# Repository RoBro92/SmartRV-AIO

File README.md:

# SmartRV AIO
**A ESP32 based smart home control board for a Camper/RV**

All feature requests are tracked in the GitHub issue tracker. 
[Feature Requests](https://github.com/RoBro92/feature-requests/issues)

This AIO board is planned to be able to work standalone or as part of a connected smart home network within a camper or RV. It will be designed based on suggestions from the community. As technology advances many are looking to automate tasks in day to day life, your recreational vehicle should be no different. Many existing monitoring systems are generally either very dated, or not very smart. This board will facilitate an all in one monitoring and control hub. 

The module has been kept as compact as possible and allows for a direct connection to 12v or 24v vehicle systems. 

**If you want to support the development you can purchase this board as a DIY kit or assembled from my Ko-Fi Shop [SmartRV Shop](https://ko-fi.com/smartrv/shop)**

## **I have developed two seperate versions of this module**

[AIO1 is THT and is suitable for at home soldering](#aio1)

[AIO2 is SMD and is designed to be assembled by a PCB manufacturer](#aio2)

###AIO1

# **THT Version 0.1**
This is the pre production initial design files with planned features and initial designs.

# **Features**
- [x] - ESP32 Microcontroller
- [x] - Individually controlled relays
- [x] - Input buttons 
- [x] - Tank temperature inputs
- [x] - Tank level inputs
- [x] - Auxilliary temperature & humidity input
- [x] - Spotlights/LED control & dimming
- [x] - RJ45 Output to Nextion Display
- [x] - Relay 1&2 are 12v direct supply for low current device 

# **Upcoming Changes**

- [ ] - RS485 serial connection
- [ ] - Bluetooth App
- [ ] - Bluetooth connection to external modules(such as Water tank module)
- [ ] - House battery voltage
- [ ] - Main battery voltage
- [ ] - On board programming
- [ ] - MQTT integration
- [ ] - Diesel heater control 

# **Images**

<table>
  <tr>
    <td>Schematic</td>
     <td>PCB Layout</td>
  </tr>
  <tr>
    <td></td>
    <td></td>
  </tr>
 </table>

# **WARNING**
This board does not have any fuse protection as such this must be provided externally.

###AIO2

# **SMD Version 0.1**
This is the pre production SMD initial design files with planned features and initial designs.

# **Features**
- [x] - ESP32 Microcontroller
- [x] - Individually controlled relays
- [x] - Input buttons 
- [x] - Tank temperature inputs
- [x] - Tank level inputs
- [x] - Auxilliary temperature & humidity input

# **Upcoming Changes**

- [ ] - RS485 serial connection
- [ ] - Bluetooth App
- [ ] - Bluetooth connection to external modules(such as Water tank module)
- [ ] - House battery voltage
- [ ] - Main battery voltage
- [ ] - On board programming
- [ ] - MQTT integration
- [ ] - Diesel heater control 
- [ ] - RJ45 Output to Nextion Display
- [ ] - Spotlights/LED control & dimming
- [ ] - Relay 1&2 are 12v direct supply for low current device 

# **Images**

<table>
  <tr>
    <td>Schematic</td>
     <td>PCB Layout</td>
  </tr>
  <tr>
    <td></td>
    <td></td>
  </tr>
 </table>

# **WARNING**
This board does not have any fuse protection as such this must be provided externally.

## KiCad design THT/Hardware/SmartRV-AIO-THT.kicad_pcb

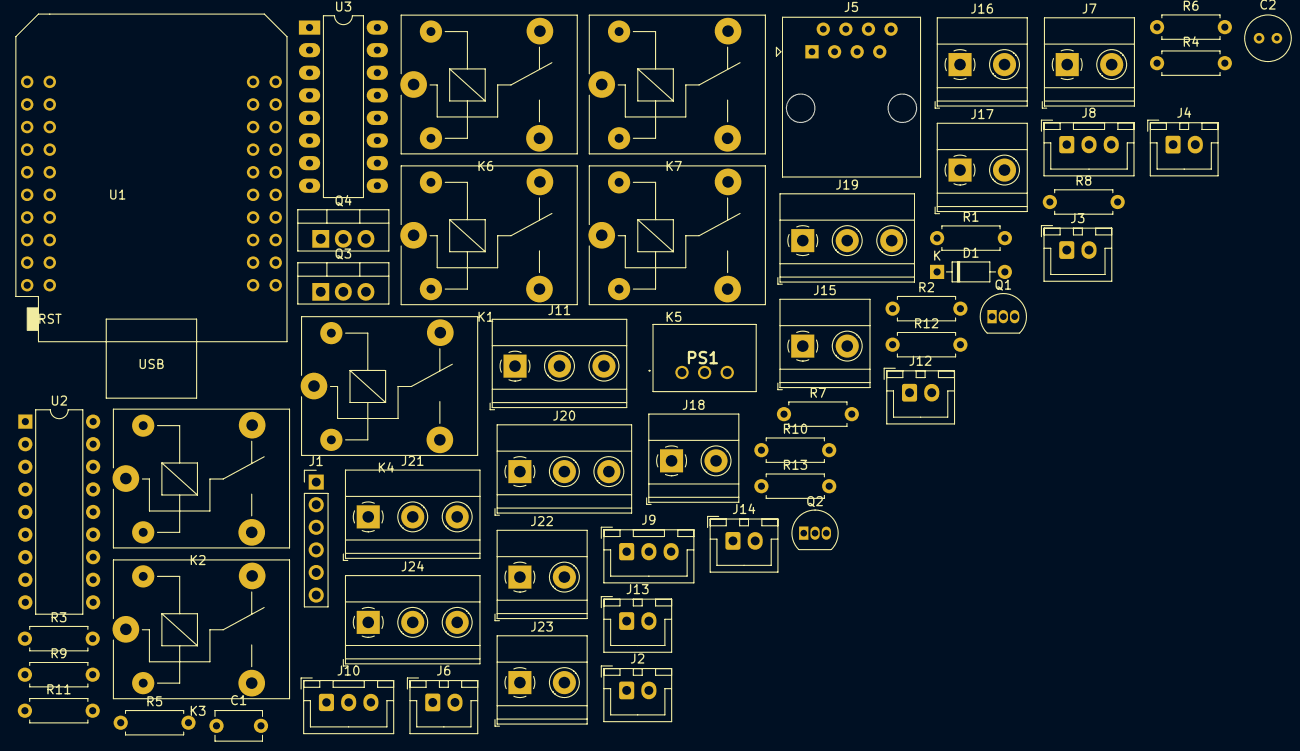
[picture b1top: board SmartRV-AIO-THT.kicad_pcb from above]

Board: 2 copper layers, 55 parts (0 on the bottom side), 57 nets, no tracks yet.

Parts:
C1: 10uF; C_Disc_D5.1mm_W3.2mm_P5.00mm
C2: 22uF; C_Radial_D5.0mm_H5.0mm_P2.00mm
D1: 1N4148; D_DO-35_SOD27_P7.62mm_Horizontal
J1: Programming Header; PinHeader_1x06_P2.54mm_Vertical
J2: Button1; JST_XH_B2B-XH-A_1x02_P2.50mm_Vertical
J3: Button2; JST_XH_B2B-XH-A_1x02_P2.50mm_Vertical
J4: Button3; JST_XH_B2B-XH-A_1x02_P2.50mm_Vertical
J5: RJ45; RJ45_Amphenol_54602-x08_Horizontal
J6: Button4; JST_XH_B2B-XH-A_1x02_P2.50mm_Vertical
J7, J15, J16, J17, J18, J22, J23: Screw_Terminal_01x02; TerminalBlock_Phoenix_MKDS-1,5-2_1x02_P5.00mm_Horizontal
J8: Temp 1; JST_XH_B3B-XH-A_1x03_P2.50mm_Vertical
J9: Temp 2; JST_XH_B3B-XH-A_1x03_P2.50mm_Vertical
J10: Temp 3; JST_XH_B3B-XH-A_1x03_P2.50mm_Vertical
J11, J19, J20, J21, J24: Screw_Terminal_01x03; TerminalBlock_Phoenix_MKDS-1,5-3_1x03_P5.00mm_Horizontal
J12, J13, J14: Water Level Sensor; JST_XH_B2B-XH-A_1x02_P2.50mm_Vertical
K1, K2, K3, K4, K5, K6, K7: Relay; Relay_SPDT_SANYOU_SRD_Series_Form_C
PS1: K7805-500R3; K7805500R3
Q1, Q2: 2N3904; TO-92_Inline
Q3, Q4: IRF540N; TO-220-3_Vertical
R1, R2, R3: 470; R_Axial_DIN0207_L6.3mm_D2.5mm_P7.62mm_Horizontal
R4, R5, R9, R10, R11, R12, R13: 10k; R_Axial_DIN0207_L6.3mm_D2.5mm_P7.62mm_Horizontal
R6, R7, R8: 4.7k; R_Axial_DIN0207_L6.3mm_D2.5mm_P7.62mm_Horizontal
U1: mini_esp32; ESP32_mini
U2: MCP23008-xP; DIP-18_W7.62mm
U3: ULN2003; DIP-16_W7.62mm_LongPads

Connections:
3v3: J8.1, J9.1, J10.1, J11.1, J19.1, R1.1, R2.1, R3.1, R4.1, R5.1, R6.1, R7.1, R8.1, R9.1, U1.16 (3V3), U2.18 (VDD)
5v: C2.1, J5.1, J5.2, K1.5, K2.5, K3.5, K4.5, K5.5, K6.5, K7.5, PS1.3 (+VO), U1.35 (VCC_(USB)), U3.9 (COM)
12v: C1.1, J7.2, J22.1, J23.2, PS1.1 (VIN)
/PWR3/20: D1.2 (A), J1.1
DHT1: J19.2, R9.2
DHT2: J11.2, R4.2
DISPRX: J5.7, J5.8, U1.31 (IO_16/D4)
DISPTX: J5.5, J5.6, U1.29 (IO_17/D3)
ESP_RX: J1.4, U1.23 (RXD)
ESP_TX: J1.3, U1.21 (TXD)
GND: C1.2, C2.2, J1.2, J2.1, J3.1, J4.1, J5.3, J5.4, J6.1, J7.1, J8.3, J9.3, J10.3, J11.3, J12.2, J13.2, J14.2, J19.3, PS1.2 (GND), Q1.1 (E), Q2.1 (E), Q3.3 (S), Q4.3 (S), U1.1 (GND), U1.22 (GND), U1.33 (GND), U2.3 (A2), U2.4 (A1), U2.5 (A0), U2.9 (VSS), U3.8 (GND)
unnamed: J15.1, K1.3
unnamed: J15.2, K1.1
unnamed: J16.1, K2.3
unnamed: J16.2, K2.1
unnamed: J17.1, K3.3
unnamed: J17.2, K3.1
unnamed: J18.1, K4.3
unnamed: J18.2, K4.1
unnamed: J20.1, K6.3
unnamed: J20.2, K6.1
unnamed: J20.3, K6.4
unnamed: J21.1, K7.3
unnamed: J21.2, K7.1
unnamed: J21.3, K7.4
unnamed: K1.2, U3.16 (O1)
unnamed: K2.2, U3.15 (O2)
unnamed: K3.2, U3.14 (O3)
unnamed: K4.2, U3.13 (O4)
unnamed: J24.2, K5.1
unnamed: K5.2, U3.12 (O5)
unnamed: J24.1, K5.3
unnamed: J24.3, K5.4
unnamed: K6.2, U3.11 (O6)
unnamed: K7.2, U3.10 (O7)
unnamed: Q1.2 (B), R10.2
unnamed: Q1.3 (C), Q3.1 (G), R12.1
unnamed: Q2.2 (B), R11.2
unnamed: Q2.3 (C), Q4.1 (G), R13.1
unnamed: J22.2, Q3.2 (D), R12.2
unnamed: J23.1, Q4.2 (D), R13.2
unnamed: R5.2, U2.6 (~RESET)
Relay1: U2.16 (GP6), U3.1 (I1)
Relay2: U2.15 (GP5), U3.2 (I2)
Relay3: U2.14 (GP4), U3.3 (I3)
Relay4: U2.13 (GP3), U3.4 (I4)
Relay5: U2.12 (GP2), U3.5 (I5)
Relay6: U2.11 (GP1), U3.6 (I6)
Relay7: U2.10 (GP0), U3.7 (I7)
SCL: U1.25 (IO_22/D1/SCL), U2.1 (SCL)
SDA: U1.27 (IO_21/D2/SDA), U2.2 (SDA)
Temp1: J8.2, R1.2
Temp2: J9.2, R2.2
Temp3: J10.2, R3.2
Water1: J12.1, R6.2
Water2: J13.1, R7.2
Water3: J14.1, R8.2

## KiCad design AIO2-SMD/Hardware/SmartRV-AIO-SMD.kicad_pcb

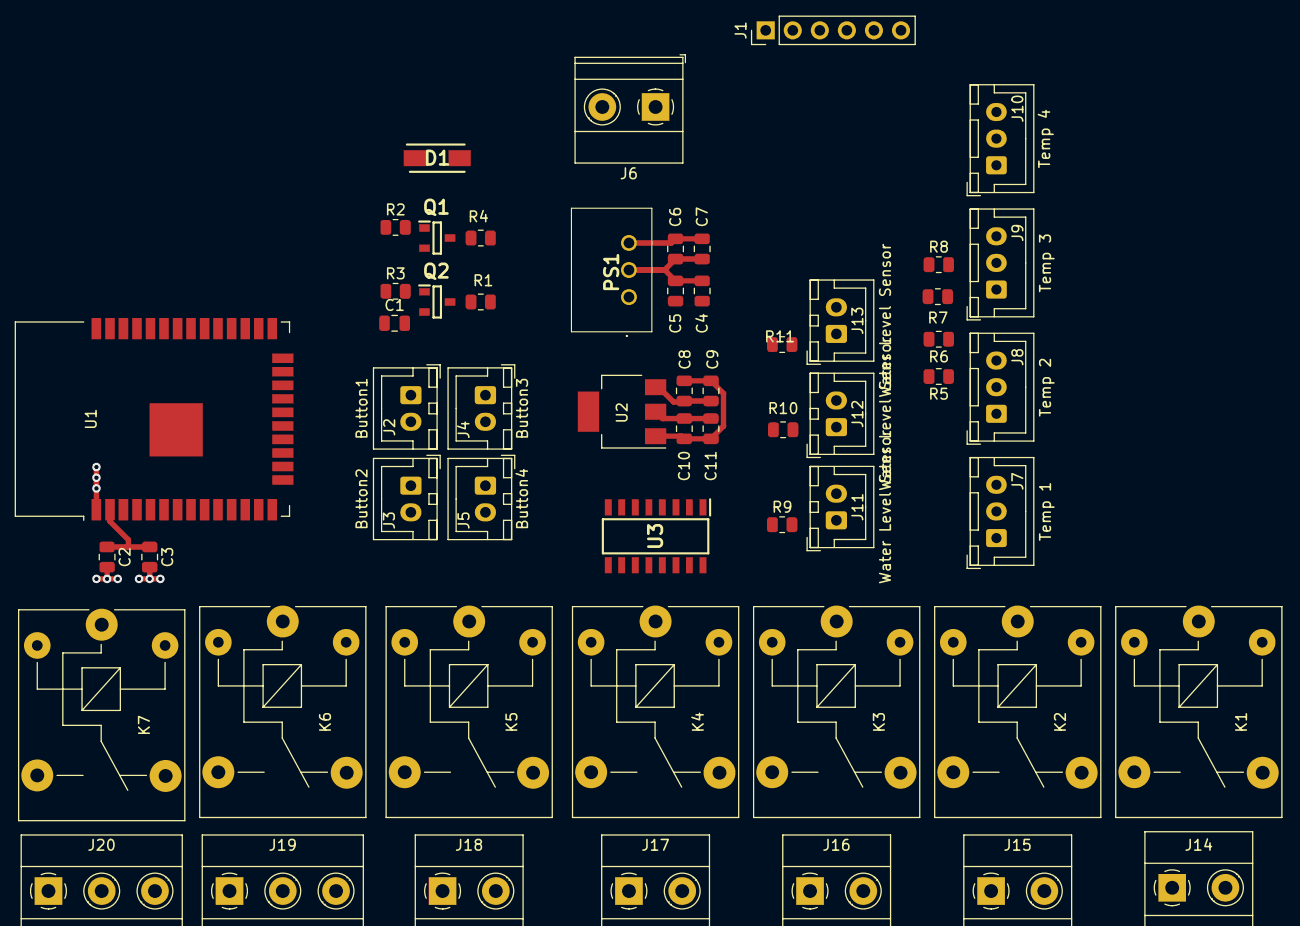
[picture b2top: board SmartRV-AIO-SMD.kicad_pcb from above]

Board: 2 copper layers, 56 parts (0 on the bottom side), 59 nets.

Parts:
C1: 100nf; C_0805_2012Metric
C2, C5: 10uF; C_0805_2012Metric
C3: 0.1uF; C_0805_2012Metric
C4, C7, C8, C9, C11: TBC; C_0805_2012Metric
C6, C10: 22uF; C_0805_2012Metric
D1: SS14; DIOM5126X250N
J1: Programming Header; PinHeader_1x06_P2.54mm_Vertical
J2: Button1; JST_XH_B2B-XH-A_1x02_P2.50mm_Vertical
J3: Button2; JST_XH_B2B-XH-A_1x02_P2.50mm_Vertical
J4: Button3; JST_XH_B2B-XH-A_1x02_P2.50mm_Vertical
J5: Button4; JST_XH_B2B-XH-A_1x02_P2.50mm_Vertical
J6, J14, J15, J16, J17, J18: Screw_Terminal_01x02; TerminalBlock_Phoenix_MKDS-1,5-2_1x02_P5.00mm_Horizontal
J7: Temp 1; JST_XH_B3B-XH-A_1x03_P2.50mm_Vertical
J8: Temp 2; JST_XH_B3B-XH-A_1x03_P2.50mm_Vertical
J9: Temp 3; JST_XH_B3B-XH-A_1x03_P2.50mm_Vertical
J10: Temp 4; JST_XH_B3B-XH-A_1x03_P2.50mm_Vertical
J11, J12, J13: Water Level Sensor; JST_XH_B2B-XH-A_1x02_P2.50mm_Vertical
J19, J20: Screw_Terminal_01x03; TerminalBlock_Phoenix_MKDS-1,5-3_1x03_P5.00mm_Horizontal
K1, K2, K3, K4, K5, K6, K7: Relay; Relay_SPDT_SANYOU_SRD_Series_Form_C
PS1: K7805-500R3; K7805500R3
Q1, Q2: MMBT2222A; SOT95P240X120-3N
R1, R2, R3, R4: 10k; R_0805_2012Metric
R5, R6, R7, R8: 470; R_0805_2012Metric
R9, R10, R11: 4.7k; R_0805_2012Metric
U1: ESP32-WROOM-32D; ESP32-WROOM-32
U2: AMS1117-3.3; SOT-223-3_TabPin2
U3: ULN2003A; SOIC127P600X175-16N

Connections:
3v3: C10.1, C11.2, R1.1, R4.1, R9.1, R10.1, R11.1, U2.2 (VO)
5v: C6.1, C7.1, C8.2, C9.1, K1.5, K2.5, K3.5, K4.5, K5.5, K6.5, K7.5, PS1.3 (+VO), U2.3 (VI), U3.9 (COM)
12v: C4.1, C5.1, J6.2, PS1.1 (VIN)
/PWR3/20: D1.2, J1.1
Button1: J2.2, U1.26 (IO4)
Button2: J3.2, U1.16 (IO13)
Button3: J4.2, U1.13 (IO14)
Button4: J5.2, U1.23 (IO15)
CTS: J1.6, Q1.2, R3.1
ESP_IO0: Q1.3, R4.2, U1.25 (IO0)
ESP_RESET: C1.2, Q2.3, R1.2, U1.3 (EN)
ESP_RX: J1.4, U1.34 (RXD0/IO3)
ESP_TX: J1.3, U1.35 (TXD0/IO1)
GND: C1.1, C2.2, C3.2, C4.2, C5.2, C6.2, C7.2, C8.1, C9.2, C10.2, C11.1, J1.2, J2.1, J3.1, J4.1, J5.1, J6.1, J7.3, J8.3, J9.3, J10.3, J11.2, J12.2, J13.2, PS1.2 (GND), U1.1 (GND), U1.15 (GND), U1.38 (GND), U1.39 (GND), U2.1 (GND), U3.8 (GND)
unnamed: J7.1, R5.1
unnamed: J8.1, R6.1
unnamed: J9.1, R7.1
unnamed: J10.1, R8.1
unnamed: J14.1, K1.3
unnamed: J14.2, K1.1
unnamed: J15.1, K2.3
unnamed: J15.2, K2.1
unnamed: J16.1, K3.3
unnamed: J16.2, K3.1
unnamed: J17.1, K4.3
unnamed: J17.2, K4.1
unnamed: J18.1, K5.3
unnamed: J18.2, K5.1
unnamed: J19.1, K6.3
unnamed: J19.2, K6.1
unnamed: J19.3, K6.4
unnamed: J20.1, K7.3
unnamed: J20.2, K7.1
unnamed: J20.3, K7.4
unnamed: K1.2, U3.16 (O1)
unnamed: K2.2, U3.15 (O2)
unnamed: K3.2, U3.14 (O3)
unnamed: K4.2, U3.13 (O4)
unnamed: K5.2, U3.12 (O5)
unnamed: K6.2, U3.11 (O6)
unnamed: K7.2, U3.10 (O7)
unnamed: Q1.1, R2.2
unnamed: Q2.1, R3.2
RTS: J1.5, Q2.2, R2.1
Relay1: U1.27 (IO16), U3.1 (I1)
Relay2: U1.28 (IO17), U3.2 (I2)
Relay3: U1.30 (IO18), U3.3 (I3)
Relay4: U1.31 (IO19), U3.4 (I4)
Relay5: U1.33 (IO21), U3.5 (I5)
Relay6: U1.36 (IO22), U3.6 (I6)
Relay7: U1.37 (IO23), U3.7 (I7)
Temp1: J7.2, R5.2, U1.10 (IO25)
Temp2: J8.2, R6.2, U1.11 (IO26)
Temp3: J9.2, R7.2, U1.12 (IO27)
Temp4: J10.2, R8.2, U1.8 (IO32)
VDD: C2.1, C3.1, D1.1, U1.2 (VDD)
Water1: J11.1, R9.2, U1.9 (IO33)
Water2: J12.1, R10.2, U1.6 (IO34)
Water3: J13.1, R11.2, U1.7 (IO35)

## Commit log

2022-03-01 Added Kicad schematic and PCB files
2022-03-02 Update LICENSE
    Update License to GNL
2022-03-02 Create gitignore
2022-03-23 updated schematic and images
2022-03-25 Added images for SMD schematic and updated main readme
2022-03-25 Resotre files from backup
2022-03-25 updated filenames
